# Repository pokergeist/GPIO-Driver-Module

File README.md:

# GPIO Driver Module

## Introduction

This project provides (4) channels of GPIO triggered low-side switching to ground. This allows low current microcontrollers to control higher current devices like LEDs, Optocouplers, Relays, etc. You can use the higher power provided by the 5V USB pin rather than the more limited current provided by the on-board 3.3V regulator and GPIO circuitry.

Rx3 is a 0Ω jumper that can be replaced by a 1206-size dropping resistor limit the current through your device.

I will provide all of the files necessary to have these boards fabricated and populated with the small SMD components. Some number of panels will be produced and made available via Assisti4ve Technology channels.

## Status

|    Date    | Status                                |
| :--------: | ------------------------------------- |
| 2022-11-19 | Introducing variants                  |
| 2022-11-16 | Initial release - unfabbed, untested. |

## ToDo List

* ~~Reset circuitry for the FeatherWing version~~.

## Variants

### Original

The Original was a quick effort related to another project to see if there was interest. Then the wheels started spinning.

### Skinny

The Skinny was a simple effort to clean up the Original board by moving half of the circuitry to the underside and centering the headers so everything was symetrical.

### QT

The QT was another variant to remove the need for the GPIO control lines from the MCU and instead make a Qwiic/STEMMA QT version with an I2C enabled I/O Expander. The Diodes Inc. PI4IOE5V9536 seems to fit the bill. Two Qwiic/STEMMA QT ports are provided for daisy-chaining. The Load header remains.

### Wing

Next came a request to fit the board to common board sizes. The (Feather) Wing was born.

### Variant Files

Details for each of the variants will appear in the README.md file in each of the board subdirectories.  Board directories will also include:

* Eagle PCB files including sch, brd, and zip file containing Gerber, centroid, and BOM files suitable for submission for board manufacturing and assembly.
* An importable Digi-Key Parts List.

## Options

I'm considering various options to give this board broader utility.

* Remove the gate pull-down resistor for a smaller board since most designs are low speed and the GPIO outputs are actively driven.
  * I may be able to do this unless the startup time required to drive the gate low is too great and we need a stronger pull-down.

* Use an I2C enabled port [expander](https://www.digikey.com/short/jd43pq03) to drive the gates. A Qwiic/STEMMA QT connector would eliminate the Trigger header and free up GPIO pins. Push-pull I/O preferred. ([D-K Search](https://www.digikey.com/short/ph7ww3hz)). **Done.**

## Mechanical Info

The board is currently 29mm square with (2) M2 mounting holes. The header are 5-conductor, 0.1"/2.54mm pitch. Hole size = 0.076"/1.93mm. The dimensional drawing is [here](boards/DriverModule/assets/dimensions.png).

The board's size could be reduced by moving circuitry for two channels to the other side of the board and moving the connectors so that they're symmetrical. Or by removing the gate pull-down resistors, or even the voltage dropping resistors. Skinny board shown below. 18x30.5mm

## Components

### MOSFET

An N-channel MOSFET provides low-side switching from the user's load to ground. 3V3 GPIO output voltage is provided to the MOSFET's gate which sinks ultra-low current. The MOSFET's Drain to Source resistance then drops below 1Ω, allowing current to flow from LOAD- through resistor Rx3 then the MOSFET (drain to source) to ground.

Key metrics:

| Parameter                    | Value      | Notes             |
| ---------------------------- | ---------- | ----------------- |
| Vdss Drain to Source Voltage | 30V MAX    |                   |
| Vgss Gate to Source Voltage  | +/-12V MAX |                   |
| Id - Drain current           | 500mA MAX  |                   |
| Pd - Power Dissipation       | 200mW MAX  |                   |
| Vgs_threshold                | 0.8-1.5V   | Vds=10V, Id=1mA   |
| Rds_on                       | 650mΩ typ. | Vgs=2.5, Id=500mA |

[Datasheet](https://media.digikey.com/pdf/Data%20Sheets/Rohm%20PDFs/RJK005N03FRA_DS.pdf)

### Resistors

Because of the MOSFET's gate capacitance, two resistors are required for each channel:

* **Rx1** - 100Ω current limiting resistor.
* **Rx2** - 100kΩ discharge resistor.

A 1206-size resistor pad at **Rx3** is fitted with a 0Ω jumper by default. If a current-limiting dropping resistor is required, replace the jumper.

## Parts List

| Location     | Part Number                                                  | Notes                                                   |
| ------------ | ------------------------------------------------------------ | ------------------------------------------------------- |
| MOSFET Qx    | Rohm [RJK005N03FRAT146](https://www.digikey.com/short/qvnjfq3w) 30 V 500mA 200mW | N-Channel 30 V 500mA (Ta) 200mW (Ta) Surface Mount SMT3 |
| Resistor Rx1 | Stackpole [RMCF0603JT100R](https://www.digikey.com/short/289f4vh8) 100Ω 5% 1/10W 0603 |                                                         |
| Resistor Rx2 | Stackpole [RMCF0603JT10K0](https://www.digikey.com/short/h7rn9qc7) 10kΩ 5% 1/10W 0603 |                                                         |
| Resistor Rx3 | Stackpole [RMCF1206ZT0R00](https://www.digikey.com/short/5hqtqvbn) 0Ω 1/4W 1206 Jumper | Replace with dropping resistor as needed.               |

## Jumper Pins

Solder pads are provided for 0.1" pitch jumpers or connectors.

### JP1

|   5    |     4     |     3     |     2     |     1     |
| :----: | :-------: | :-------: | :-------: | :-------: |
| Ground | Trigger 4 | Trigger 3 | Trigger 2 | Trigger 1 |

Connect your GPIO pin to the Trigger pin to connect your device to ground on an active high signal.

### JP2

|   5    |    4    |    3    |    2    |    1    |
| :----: | :-----: | :-----: | :-----: | :-----: |
| Ground | Load- 4 | Load- 3 | Load- 2 | Load- 1 |

Connect the cathode of your device to the LOAD- pin.

## Images

#### Original

[Original](boards/DriverModule/)

#### Skinny

[Skinny](boards/DriverModuleSkinny/)

#### QT

[QT](boards/DriverModuleQT/)

#### Wing

[Wing](boards/DriverModuleWing/)

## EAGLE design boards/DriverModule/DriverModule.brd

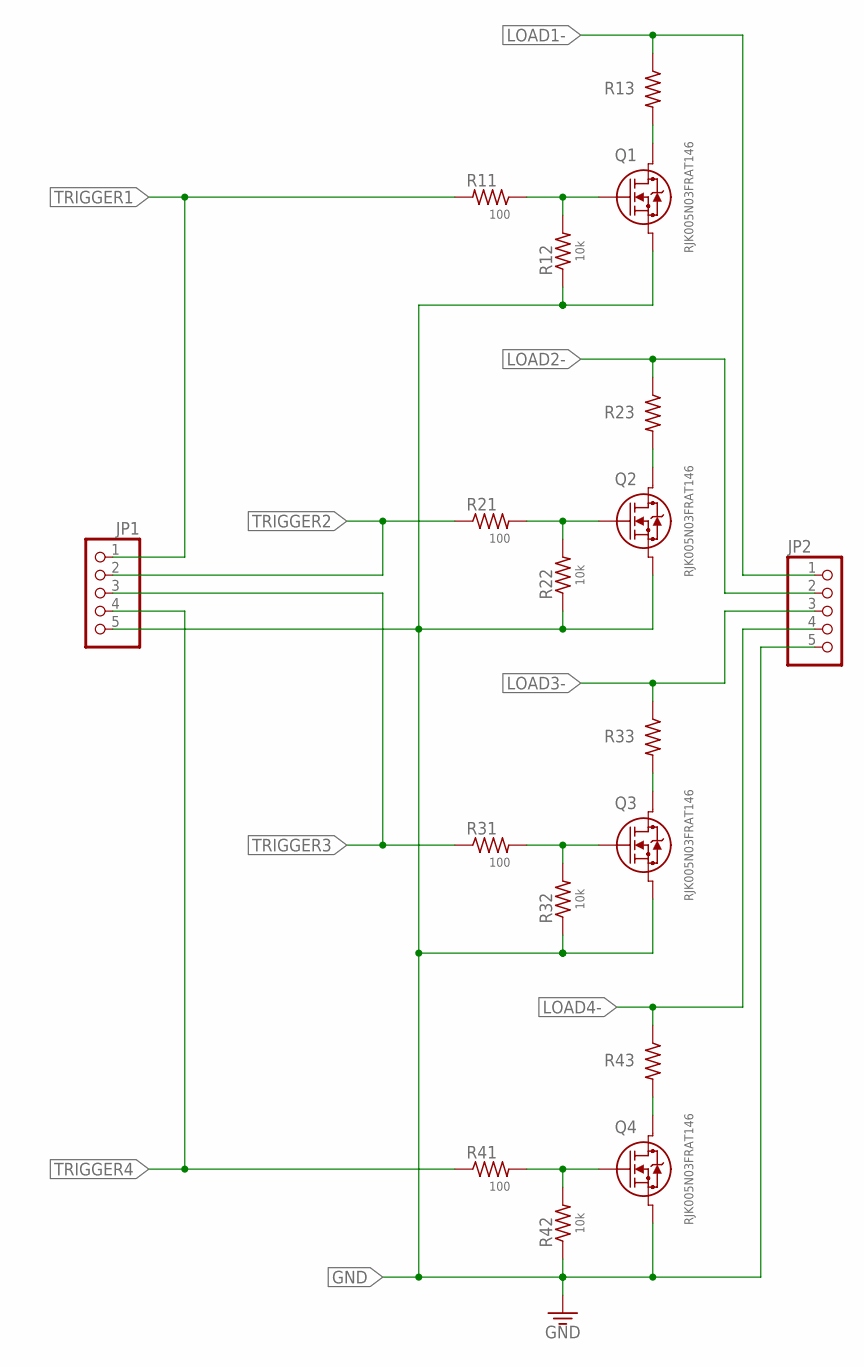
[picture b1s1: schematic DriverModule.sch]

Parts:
JP1, JP2: HEADER-1X576MIL; 1X05_ROUND_76
Q1, Q2, Q3, Q4: RJK005N03FRAT146; TRANS_RHK003N_ROM-M
R11, R21, R31, R41: 100; R0603
R12, R22, R32, R42: 10k; R0603
R13, R23, R33, R43: R-US_R1206; R1206

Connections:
GATE1: Q1.2 (1), R11.1, R12.2
GATE2: Q2.2 (1), R21.2, R22.2
GATE3: Q3.2 (1), R31.2, R32.2
GATE4: Q4.2 (1), R41.2, R42.2
GND: JP1.5, JP2.5, Q1.3, Q2.3, Q3.3, Q4.3, R12.1, R22.1, R32.1, R42.1
LD-: Q4.1 (2), R43.2
LD-1: Q3.1 (2), R33.2
LD-2: Q2.1 (2), R23.2
LD-3: Q1.1 (2), R13.2
LOAD1-: JP2.1, R13.1
LOAD2-: JP2.2, R23.1
LOAD3-: JP2.3, R33.1
LOAD4-: JP2.4, R43.1
TRIGGER1: JP1.1, R11.2
TRIGGER2: JP1.2, R21.1
TRIGGER3: JP1.3, R31.1
TRIGGER4: JP1.4, R41.1

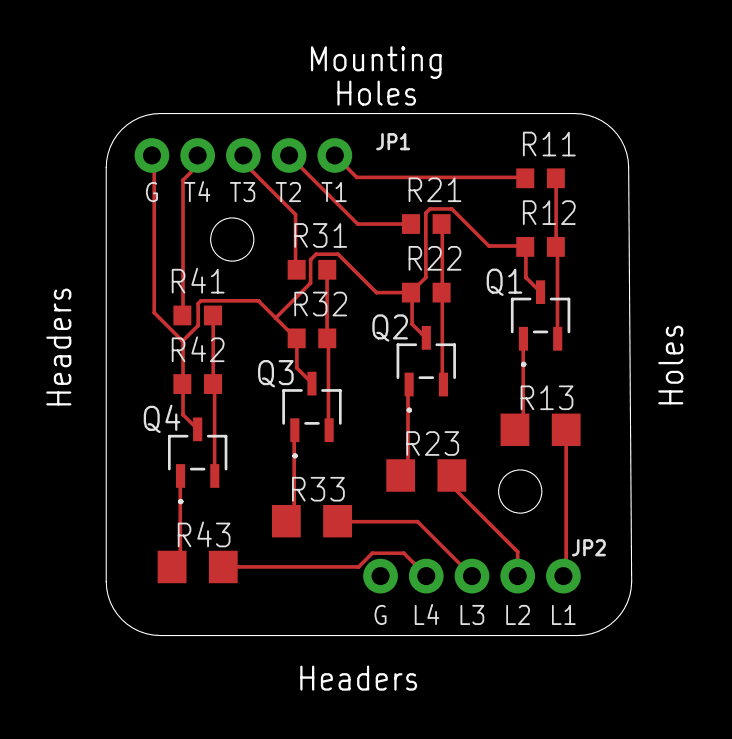
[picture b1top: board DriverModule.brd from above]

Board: 2 copper layers, 36.7 x 37.1 mm, 18 parts (0 on the bottom side), 17 nets.

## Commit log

2022-11-17 first CI
2022-11-17 todo list
2022-11-17 dimensions & labels
2022-11-17 options
2022-11-17 skinny version
2022-11-19 new boards
2022-11-19 img link
2022-11-20 more + reorg
2022-11-20 Wing img
2022-11-20 orig pcb

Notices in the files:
parts and their libraries:
microbuilder: This work is placed in the public domain, and may be freely used for commercial and non-commercial work with the following conditions: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
COPYRIGHT: Copyright (C) 2022 Ultra Librarian. All rights reserved.
